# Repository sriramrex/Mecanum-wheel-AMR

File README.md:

# Mecanum-wheel-AMR

Built a 3D-printed Mecanum-wheel AMR with four independently driven wheels, controlled via Raspberry Pi and a custom RC interface for holonomic motion.
Implemented a closed-loop PID velocity controller using L293D H-bridge drivers and geared DC motors to achieve stable torque–speed characteristics and precise omnidirectional manoeuvring.

Here is the completed Model of the AMR

All 3D-printable STL files used in this project are publicly available on Thingiverse:  
👉 [Thingiverse Model – 3D Printable Files](https://www.thingiverse.com/thing:4023557)

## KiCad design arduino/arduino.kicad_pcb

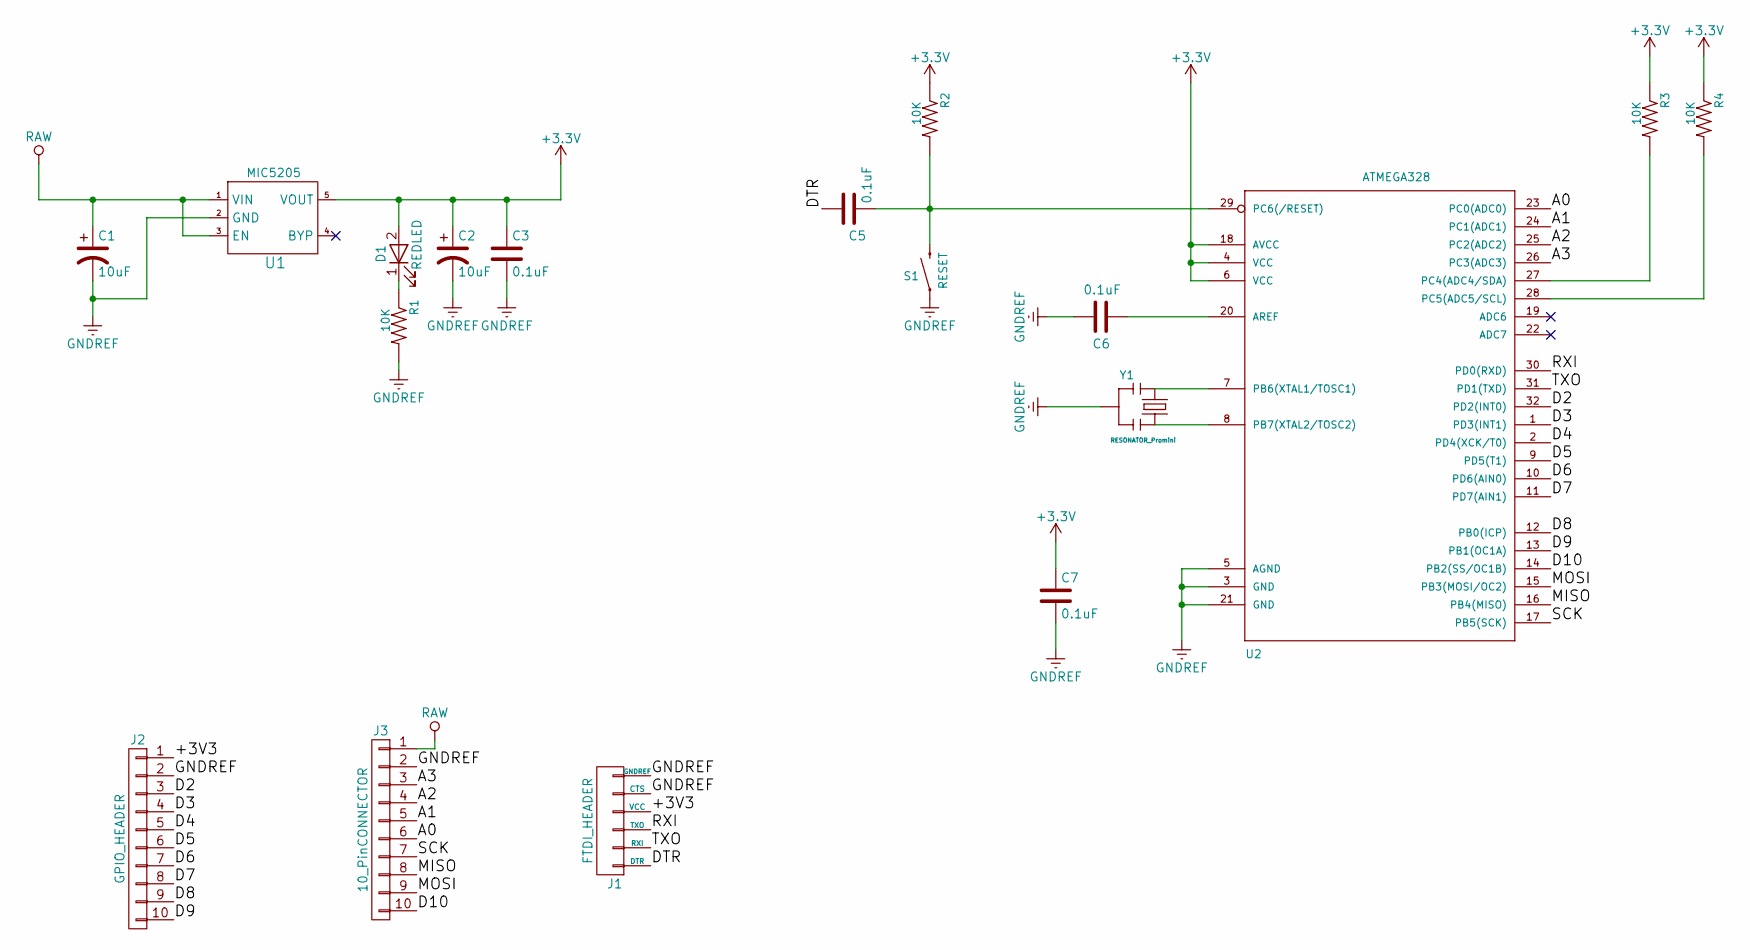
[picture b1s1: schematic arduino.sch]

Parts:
C1, C2: 10uF; Polarized Capacitor
C3, C6, C7: 0.1uF; Capacitor_0402
C5: 0.1uF; Capacitor_0603
D1: REDLED; LED_0603
J1: FTDI_HEADER; Pin_Header_1X06
J2: GPIO_HEADER; Pin_Header_1X10
J3: 10_PinCONNECTOR; Pin_Header_1X10
R1, R2, R3, R4: 10K; Resistor_0603
S1: RESET; RESET SWITCH
U1: MIC5205
U2: ATMEGA328; ATMEGA328_TQFP32-08
Y1: RESONATOR_Promini; RESONATOR-SMD

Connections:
/A0: J3.6, U2.23 (PC0(ADC0))
/A1: J3.5, U2.24 (PC1(ADC1))
/A2: J3.4, U2.25 (PC2(ADC2))
/A3: J3.3, U2.26 (PC3(ADC3))
/D2: J2.3, U2.32 (PD2(INT0))
/D3: J2.4, U2.1 (PD3(INT1))
/D4: J2.5, U2.2 (PD4(XCK/T0))
/D5: J2.6, U2.9 (PD5(T1))
/D6: J2.7, U2.10 (PD6(AIN0))
/D7: J2.8, U2.11 (PD7(AIN1))
/D8: J2.9, U2.12 (PB0(ICP))
/D9: J2.10, U2.13 (PB1(OC1A))
/D10: J3.10, U2.14 (PB2(SS/OC1B))
/DTR: C5.1, J1.1 (DTR)
/MISO: J3.8, U2.16 (PB4(MISO))
/MOSI: J3.9, U2.15 (PB3(MOSI/OC2))
/RXI: J1.3 (TXO), U2.30 (PD0(RXD))
/SCK: J3.7, U2.17 (PB5(SCK))
/TXO: J1.2 (RXI), U2.31 (PD1(TXD))
GNDREF: C1.2, C2.2, C3.2, C6.2, C7.2, J1.5 (CTS), J1.6 (GNDREF), J2.2, J3.2, R1.2, S1.1, U1.2 (GND), U2.3 (GND), U2.5 (AGND), U2.21 (GND), Y1.2
unnamed: C5.2, R2.2, S1.2, U2.29 (PC6(/RESET))
unnamed: C6.1, U2.20 (AREF)
unnamed: D1.1 (K), R1.1
unnamed: R3.2, U2.27 (PC4(ADC4/SDA))
unnamed: R4.2, U2.28 (PC5(ADC5/SCL))
unnamed: U2.7 (PB6(XTAL1/TOSC1)), Y1.1
unnamed: U2.8 (PB7(XTAL2/TOSC2)), Y1.3
RAW: C1.1, J3.1, U1.1 (VIN), U1.3 (EN)

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
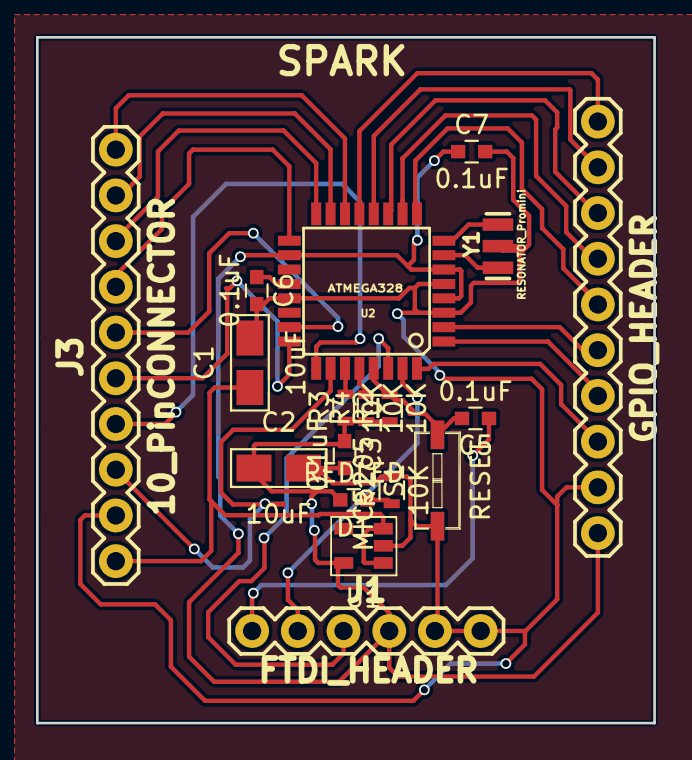
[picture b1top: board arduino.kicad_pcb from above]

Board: 2 copper layers, 34.3 x 38.1 mm, 18 parts (0 on the bottom side), 29 nets.

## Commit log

2025-12-11 Added files via uplaoad
2025-12-11 Update README with project details and image
    Added project description and image for Mecanum-wheel AMR.
2025-12-12 Include Thingiverse link in README
    Added link to Thingiverse for 3D-printable STL files.
